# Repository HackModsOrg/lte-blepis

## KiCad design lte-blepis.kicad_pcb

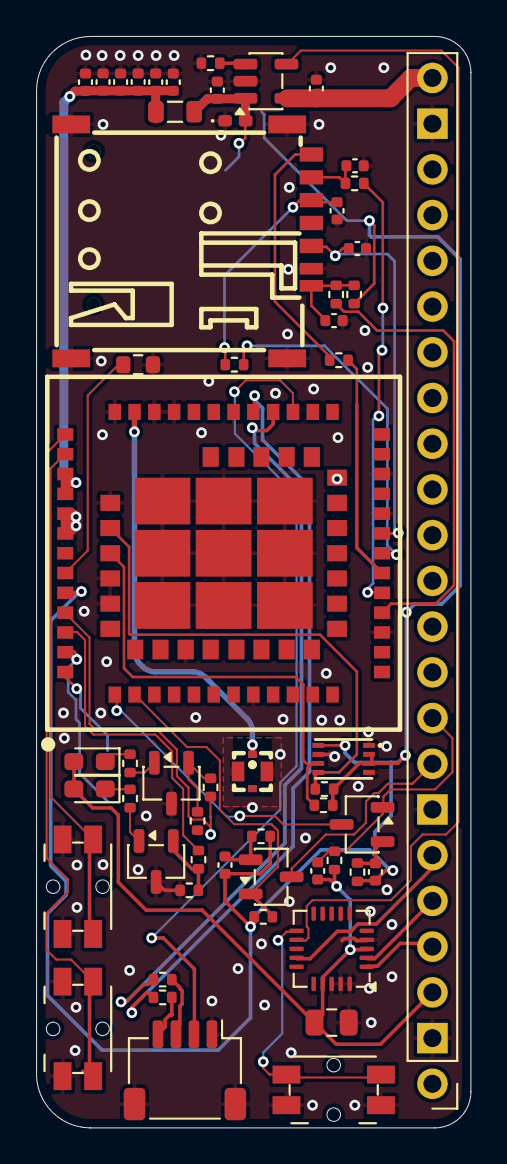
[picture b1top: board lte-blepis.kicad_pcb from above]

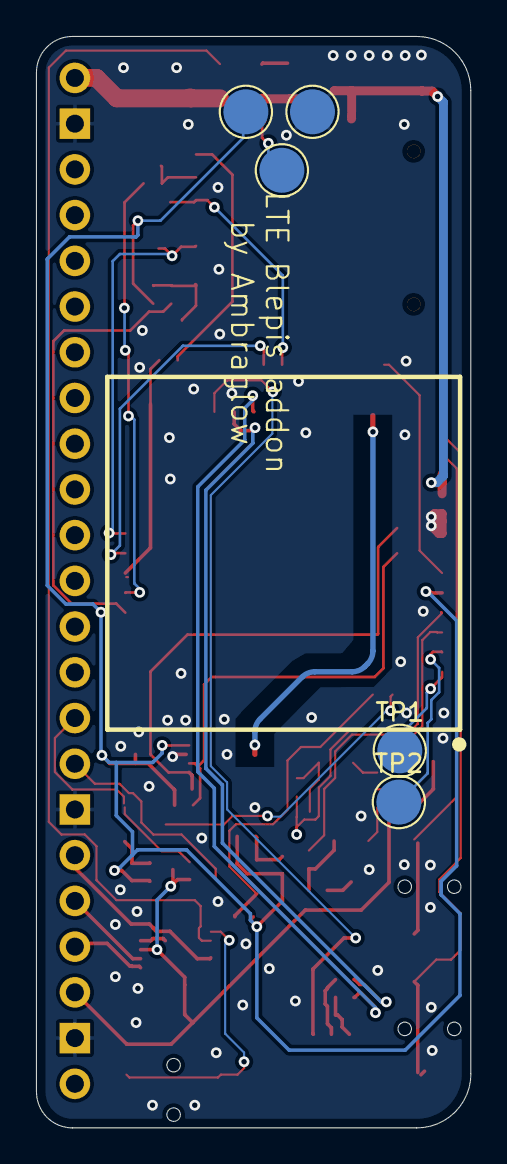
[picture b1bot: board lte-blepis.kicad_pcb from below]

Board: 2 copper layers, 24.1 x 60.6 mm, 61 parts (5 on the bottom side), 48 nets.

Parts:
C1: 1u; C_0805_2012Metric
C2: 100n; C_0402_1005Metric
C3, C4: 10uF; C_0402_1005Metric
C5: 10p; C_0402_1005Metric
C6: 33p; C_0402_1005Metric
C7: 1u; C_0402_1005Metric
C8: 10u; C_0402_1005Metric
C9, C10: 100u; C_0402_1005Metric
C11, C12, C13: 1n; C_0402_1005Metric
C14, C15, C16: 22p; C_0402_1005Metric
Card1: SMN-303; SIM-SMD_SMN-303
D1, D2: LED1; LED_0603_1608Metric_Pad1.05x0.95mm_HandSolder
D5: D_TVS_Small; D_0402_1005Metric_Pad0.77x0.64mm_HandSolder
J1: MODEM_USB; JST_SH_SM04B-SRSS-TB_1x04-1MP_P1.00mm_Horizontal
J53: EXP; PinHeader_1x23_P2.54mm_Vertical
JP1: Jumper_2_Small_Bridged; R_0603_1608Metric
L1: 30Ω@100MHz 1 Line Ferrite Bead 0805 4A 14mΩ; L_0805_2012Metric
Q1, Q2, Q3, Q4: NPN; SOT-23-3
R1, R17, R20: 2.2k; R_0402_1005Metric
R2: 3.7k; R_0402_1005Metric
R3, R14, R15, R16: 22; R_0402_1005Metric
R4, R8, R9, R10, R11, R12, R13, R18: 4.7k; R_0402_1005Metric
R5, R19: 47k; R_0402_1005Metric
R6, R7: 0; R_0402_1005Metric
RF1: ECT818011998; IPEX-SMD_ECT818011998
SW1, SW2, SW3: EVQPUL02K; Panasonic_EVQPUL_EVQPUC
TP1, TP2, TP3, TP5, TP6: TestPoint; TestPoint_Pad_D2.5mm
U1: A7682E; COMM-SMD_A7682E
U2: MCP23008-xML; QFN-20-1EP_4x4mm_P0.5mm_EP2.7x2.7mm
U4: BL24C32A-NTRC; DFN-8_L3.0-W2.0-P0.50-BL-EP
U5: SY6280AAAC; SOT-23-5

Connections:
+3V3PI_p: C1.1, C12.1, D1.2 (A), D2.2 (A), J53.3, R11.1, U2.4 (~RESET), U2.18 (VDD)
+VBAT_p: C3.1, J53.23, U5.5 (IN)
/BOOT_CFG: SW2.2 (B), U1.82 (BOOT_CFG●)
/DBG_RXD: TP2.1, U1.84 (DBG_RXD)
/DBG_TXD: TP1.1, U1.85 (DBG_TXD)
/MODEM_RST: SW1.2 (B), U1.83 (RESET)
/MODEM_SCL: R9.2, U1.65 (SCL), U4.6 (SCL)
/MODEM_SDA: R8.2, U1.64 (SDA), U4.5 (SDA)
/MODEM_USB_DN: R6.1, U1.26 (USB_DM)
/MODEM_USB_DP: R7.1, U1.25 (USB_DP)
/MODEM_VBAT: C4.1, D5.2 (A2), L1.1, TP6.1, U5.1 (OUT)
/NETLIGHT: R4.1, U1.41 (NETLIGHT)
/PWR: SW3.2 (B), U2.10 (GP1)
/Pi_GPIO4: J53.6, U2.7 (INT)
/Pi_GPIO14_p: J53.8, Q3.3 (E)
/Pi_GPIO15_p: C12.2, J53.9, Q2.1 (C), R11.2
/Pi_SCLr: J53.5, U2.19 (SCL)
/Pi_SDAr: J53.4, U2.20 (SDA)
/SIM1_CLK: Card1.C3 (CLK), R3.1
/SIM1_DET: C15.1, Card1.CD, R15.1, R17.1
/SIM1_IO: C14.1, Card1.C7 (I/O), R14.1
/SIM1_RST: C16.1, Card1.C2 (RST), R16.2
/SIM1_VDD: C2.1, Card1.C1 (VCC), U1.18 (SIM1_VDD)
/STATUS: R18.1, U1.42 (STATUS)
/SY_EN: U2.9 (GP0), U5.4 (EN)
/UART1_RXD: Q3.1 (C), R13.2, U1.2 (UART1_RXD)
/UART1_TXD: Q2.3 (E), U1.1 (UART1_TXD)
/USB_DN: J1.4, R6.2
/USB_DP: J1.3, R7.2
/USB_VBUS: J1.2, U1.24 (USB_VBUS)
GND: C1.2, C2.2, C3.2, C4.2, C5.2, C6.2, C7.2, C8.2, C9.2, C10.2, C14.2, C15.2, C16.2, Card1.8 (EP), Card1.9 (EP), Card1.10 (EP), Card1.11 (EP), Card1.C5 (GND), D5.1 (A1), J1.1, J1.MP (MountPin), J53.2, J53.7, J53.22, JP1.1 (A), Q1.3 (E), Q4.3 (E), R2.2, R5.1, R19.1, RF1.3 (GND), RF1.4 (GND), SW1.1 (A), SW2.1 (A), SW3.1 (A), TP3.1, U1.8 (GND), U1.13 (GND), U1.19 (GND), U1.21 (GND), U1.27 (GND), U1.30 (GND), U1.31 (GND), U1.33 (GND), U1.36 (GND), U1.37 (GND), U1.45 (GND), U1.63 (GND), U1.66 (GND), U1.67 (GND), U1.69 (GND), U1.70 (GND), U1.71 (GND), U1.72 (GND), U1.73 (GND), U1.74 (GND), U1.75 (GND), U1.76 (GND), U1.77 (GND), U2.1 (A2), U2.2 (A1), U2.3 (A0), U2.17 (VSS), U4.1 (A0), U4.4 (GND), U4.7 (WP), U5.2 (GND)
unnamed: C5.1, C6.1, C7.1, C8.1, C9.1, C10.1, L1.2, U1.34 (VBAT), U1.35 (VBAT)
unnamed: D1.1 (K), R1.2
unnamed: D2.1 (K), R20.2
unnamed: JP1.2 (B), U1.39 (PWRKEY)
unnamed: Q1.2 (B), R4.2, R5.2
unnamed: Q1.1 (C), R1.1
unnamed: C11.2, Q2.2 (B), R10.2
unnamed: C13.2, Q3.2 (B), R12.2
unnamed: Q4.2 (B), R18.2, R19.2
unnamed: Q4.1 (C), R20.1
unnamed: RF1.1 (IN), U1.32 (RF_ANT)
unnamed: R3.2, U1.16 (SIM1_CLK)
unnamed: R14.2, U1.15 (SIM1_DATA)
unnamed: R15.2, U1.14 (SIM1_DET)
unnamed: R16.1, U1.17 (SIM1_RST)
unnamed: R2.1, U5.3 (ISET)
VDD_EXT: C11.1, C13.1, R8.1, R9.1, R10.1, R12.1, R13.1, R17.2, TP5.1, U1.40 (VDD_EXT), U4.2 (A1), U4.3 (A2), U4.8 (VCC)

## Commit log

2026-02-03 upload files
2026-02-03 edit README
2026-02-03 refactor: flip design, flip footprints, re-do routing
2026-02-19 flip sd card footprint to correct orientation, re-do wiring
2026-02-19 tidy up test points and traces
